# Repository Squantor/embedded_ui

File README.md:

# General purpose embedded user interface
This repository contains the files for a general purpose embedded system user interface.
## Structure
* [Electronics](https://github.com/Squantor/embedded_ui/blob/master/electronics/README.md) contains the UI PCB with LCD and buttons
* [Software](https://github.com/Squantor/embedded_ui/blob/master/software/README.md) contains the test and demo software for the user interface
* [Mechanical](https://github.com/Squantor/embedded_ui/blob/master/mechanical/README.md) contains drawings of UI covers
## Checking out
This project makes extensive use of submodules, use ```git clone --recurse-submodules https://github.com/Squantor/$(PROJECT).git``` to clone the repository and its submodules in one go.

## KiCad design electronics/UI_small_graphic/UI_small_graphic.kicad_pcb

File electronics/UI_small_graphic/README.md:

# Small graphical user interface
This PCB is a small graphical user interface with a few buttons.
# HSI (Hardware Software Interface)
This applies to a project that has a embedded software component. Describe what each pin/bus does, what it is connected to, what its function is and some "safe" behaviour when starting up.
## TODO's
Still some things need to be done:
* Produce at [Aisler](https://aisler.net/)
* Assemble
* Test & characterise
* update Readme.md with pictures and BOM
## BOM
* The standard aliexpress OLED displays with 128x64 or 128x32 resolution.
* I2C port expander (PCF device)
## Pictures
TODO

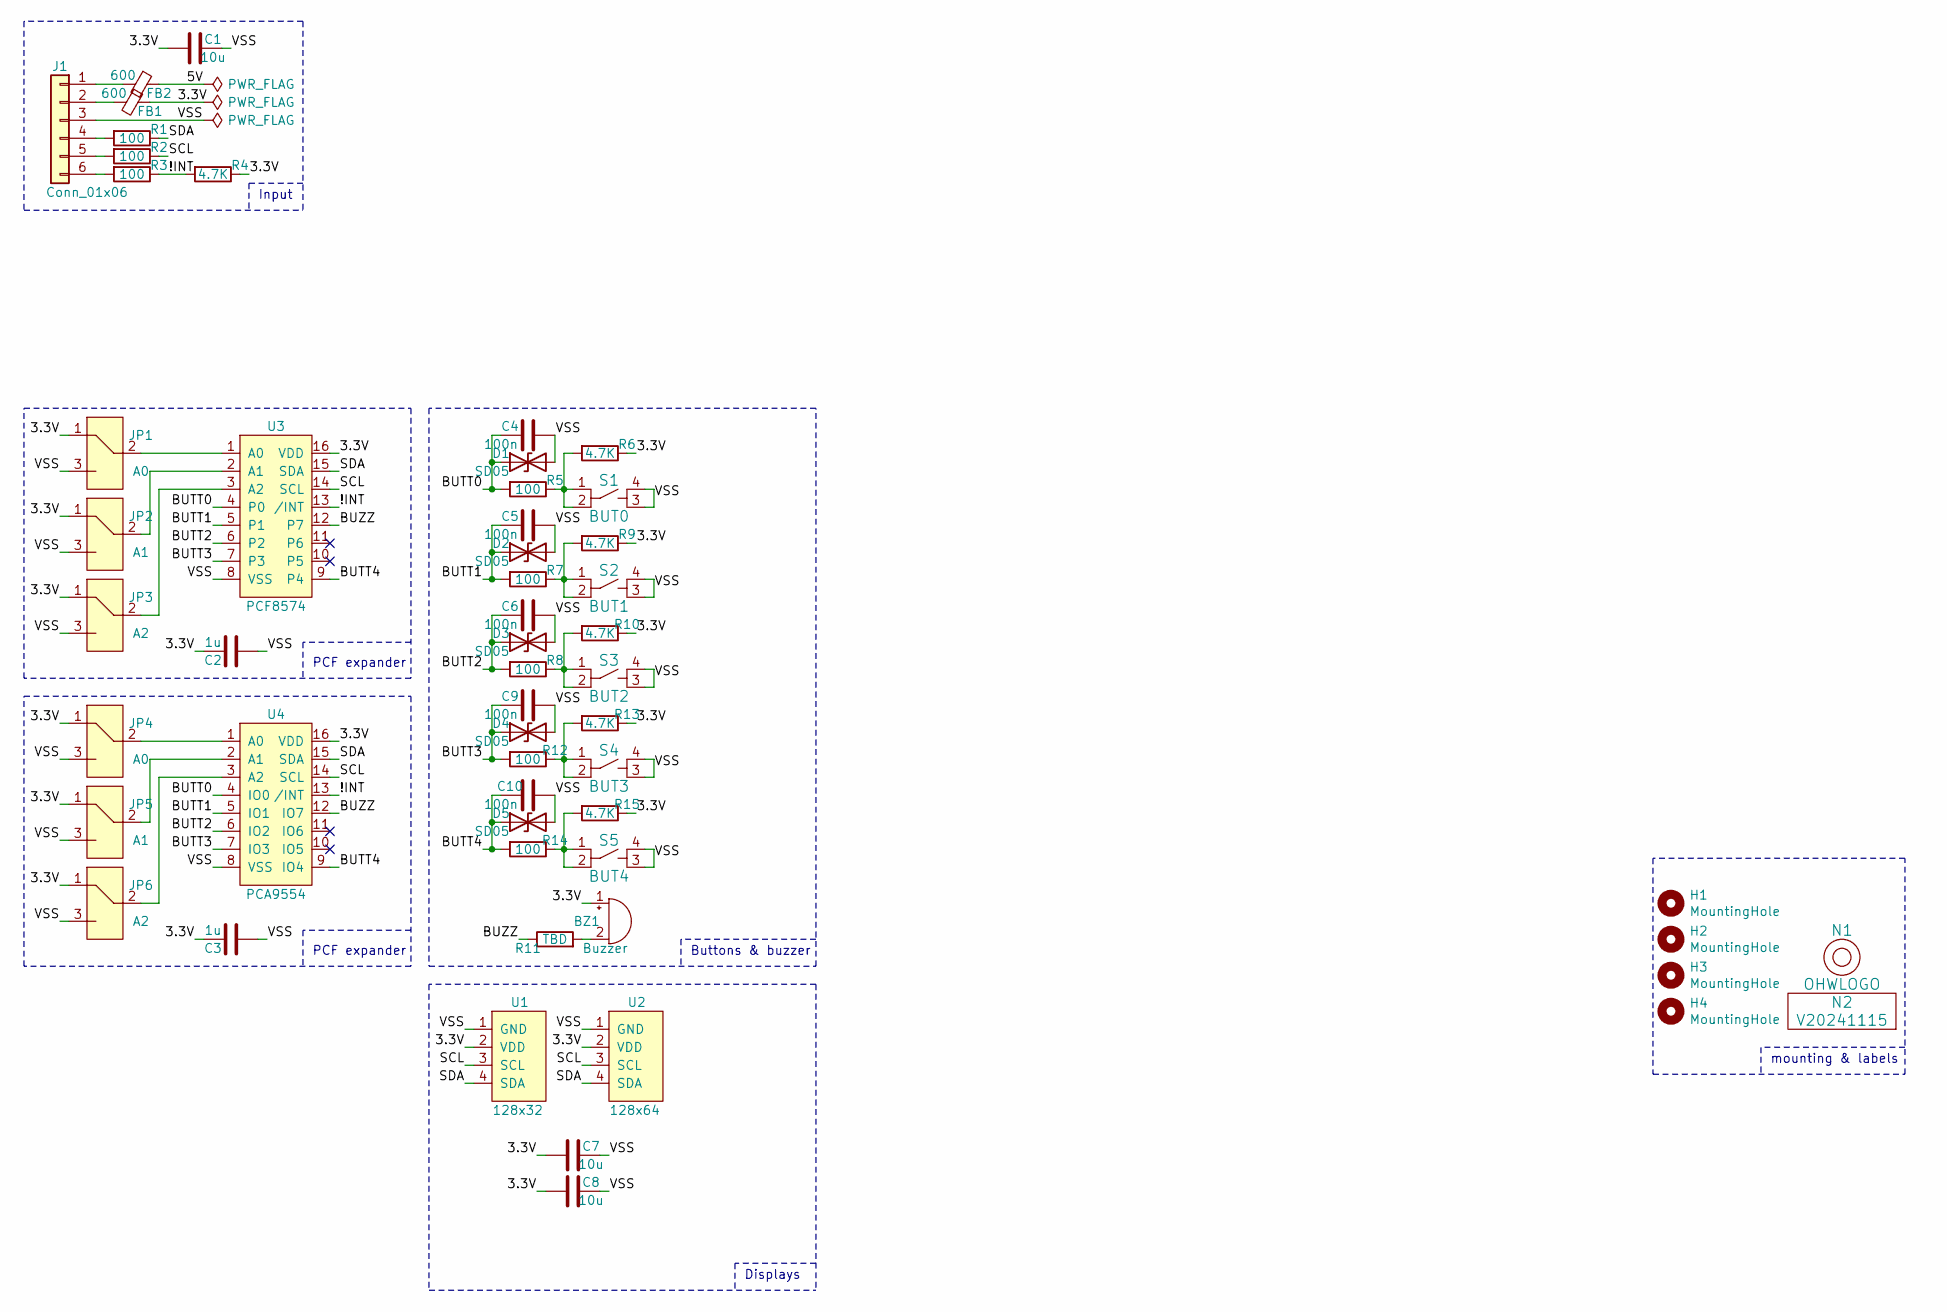
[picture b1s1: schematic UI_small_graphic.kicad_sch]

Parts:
BZ1: Buzzer; Buzzer_12x9.5RM7.6
C1, C7, C8: 10u; C_0603
C2, C3: 1u; C_0603
C4, C5, C6, C9, C10: 100n; C_0603
D1, D2, D3, D4, D5: SD05; SOD_323_onsemi
FB1, FB2: 600; L_0603
H1, H2, H3, H4: MountingHole; MountingHole_3.2mm_M3_Pad_Via
J1: Conn_01x06; JST_PH_S6B-PH-K_1x06_P2.00mm_Horizontal
JP1, JP4: A0; solder_jumper_0603_3way_12conn
JP2, JP5: A1; solder_jumper_0603_3way_12conn
JP3, JP6: A2; solder_jumper_0603_3way_12conn
N1: OHWLOGO; OSHW-Symbol_6.7x6mm_SilkScreen
N2: V20241115; Label_Generic
R1, R2, R3, R5, R7, R8, R12, R14: 100; R_0603_hand
R4, R6, R9, R10, R13, R15: 4.7K; R_0603_hand
R11: TBD; R_0603_hand
S1: BUT0; Omron_B3F-1052
S2: BUT1; Omron_B3F-1052
S3: BUT2; Omron_B3F-1052
S4: BUT3; Omron_B3F-1052
S5: BUT4; Omron_B3F-1052
U1: 128x32; OLED_128x32
U2: 128x64; OLED_132in_128x96
U3: PCF8574; SOT162-1-NXP
U4: PCA9554; SOT403-1-NXP

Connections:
/3.3V: BZ1.1 (-), C1.2, C2.1, C3.1, C7.2, C8.2, FB1.1, JP1.1, JP2.1, JP3.1, JP4.1, JP5.1, JP6.1, R4.1, R6.1, R9.1, R10.1, R13.1, R15.1, U1.2 (VDD), U2.2 (VDD), U3.16 (VDD), U4.16 (VDD)
/5V: FB2.1
/!INT: R3.1, R4.2, U3.13 (/INT), U4.13 (/INT)
/BUTT0: C4.1, D1.1 (A1), R5.2, U3.4 (P0), U4.4 (IO0)
/BUTT1: C5.1, D2.1 (A1), R7.2, U3.5 (P1), U4.5 (IO1)
/BUTT2: C6.1, D3.1 (A1), R8.2, U3.6 (P2), U4.6 (IO2)
/BUTT3: C9.1, D4.1 (A1), R12.2, U3.7 (P3), U4.7 (IO3)
/BUTT4: C10.1, D5.1 (A1), R14.2, U3.9 (P4), U4.9 (IO4)
/BUZZ: R11.1, U3.12 (P7), U4.12 (IO7)
/SCL: R2.1, U1.3 (SCL), U2.3 (SCL), U3.14 (SCL), U4.14 (SCL)
/SDA: R1.1, U1.4 (SDA), U2.4 (SDA), U3.15 (SDA), U4.15 (SDA)
/VSS: C1.1, C2.2, C3.2, C4.2, C5.2, C6.2, C7.1, C8.1, C9.2, C10.2, D1.2 (A2), D2.2 (A2), D3.2 (A2), D4.2 (A2), D5.2 (A2), J1.3, JP1.3, JP2.3, JP3.3, JP4.3, JP5.3, JP6.3, S1.3, S1.4, S2.3, S2.4, S3.3, S3.4, S4.3, S4.4, S5.3, S5.4, U1.1 (GND), U2.1 (GND), U3.8 (VSS), U4.8 (VSS)
unnamed: BZ1.2 (+), R11.2
unnamed: FB1.2, J1.2
unnamed: FB2.2, J1.1
unnamed: J1.4, R1.2
unnamed: J1.5, R2.2
unnamed: J1.6, R3.2
unnamed: JP1.2, U3.1 (A0)
unnamed: JP2.2, U3.2 (A1)
unnamed: JP3.2, U3.3 (A2)
unnamed: JP4.2, U4.1 (A0)
unnamed: JP5.2, U4.2 (A1)
unnamed: JP6.2, U4.3 (A2)
unnamed: R5.1, R6.2, S1.1, S1.2
unnamed: R7.1, R9.2, S2.1, S2.2
unnamed: R8.1, R10.2, S3.1, S3.2
unnamed: R12.1, R13.2, S4.1, S4.2
unnamed: R14.1, R15.2, S5.1, S5.2

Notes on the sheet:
Input
mounting & labels
PCF expander
Buttons & buzzer
Displays

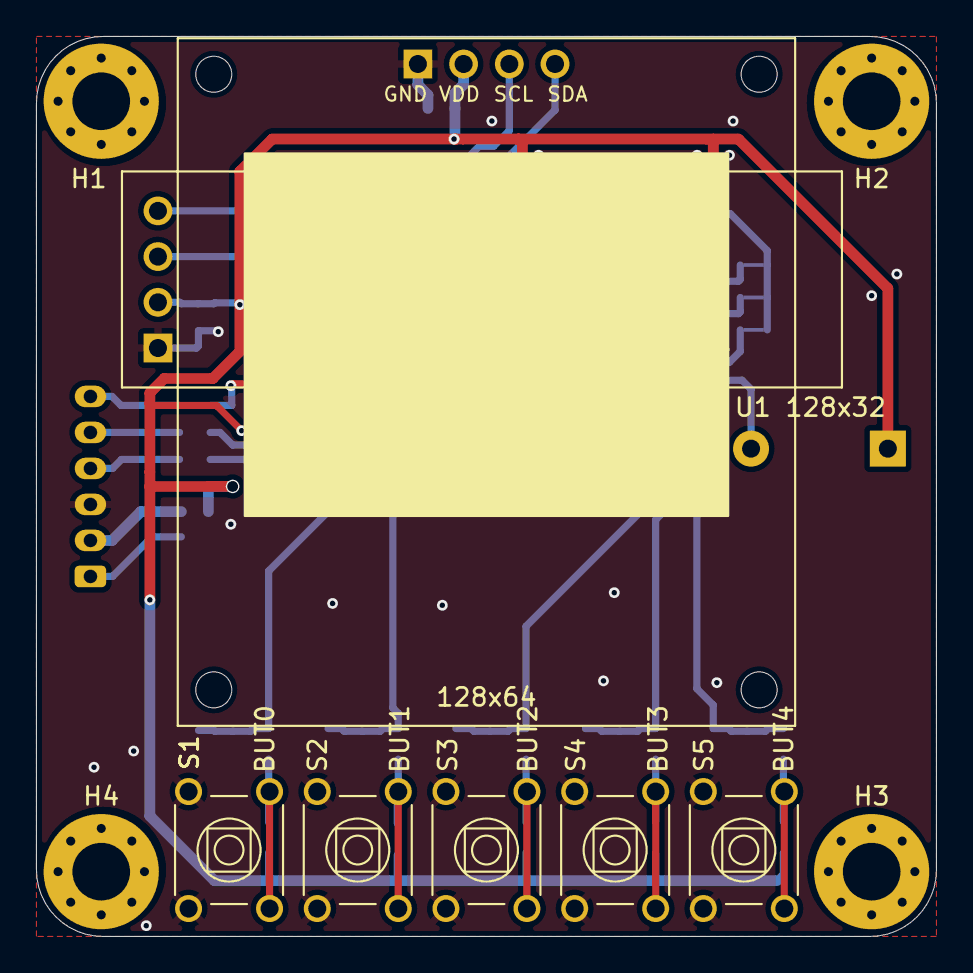
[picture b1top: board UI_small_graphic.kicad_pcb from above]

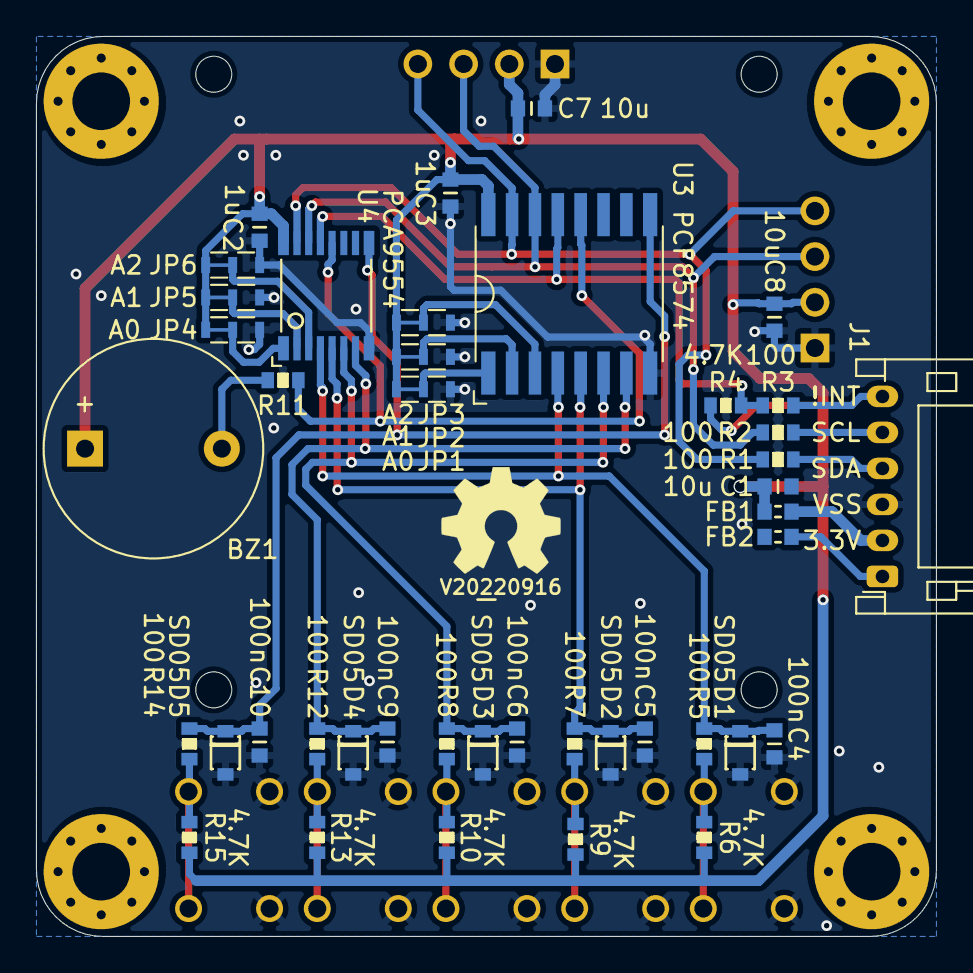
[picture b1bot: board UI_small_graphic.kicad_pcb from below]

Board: 2 copper layers, 50.0 x 50.0 mm, 55 parts (44 on the bottom side), 28 nets.

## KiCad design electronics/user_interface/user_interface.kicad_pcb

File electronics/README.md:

# Embedded User Interface hardware
Electronics for a embedded user interface.
* [user interface](user_interface/README.md) is a simple user interface for various projects.

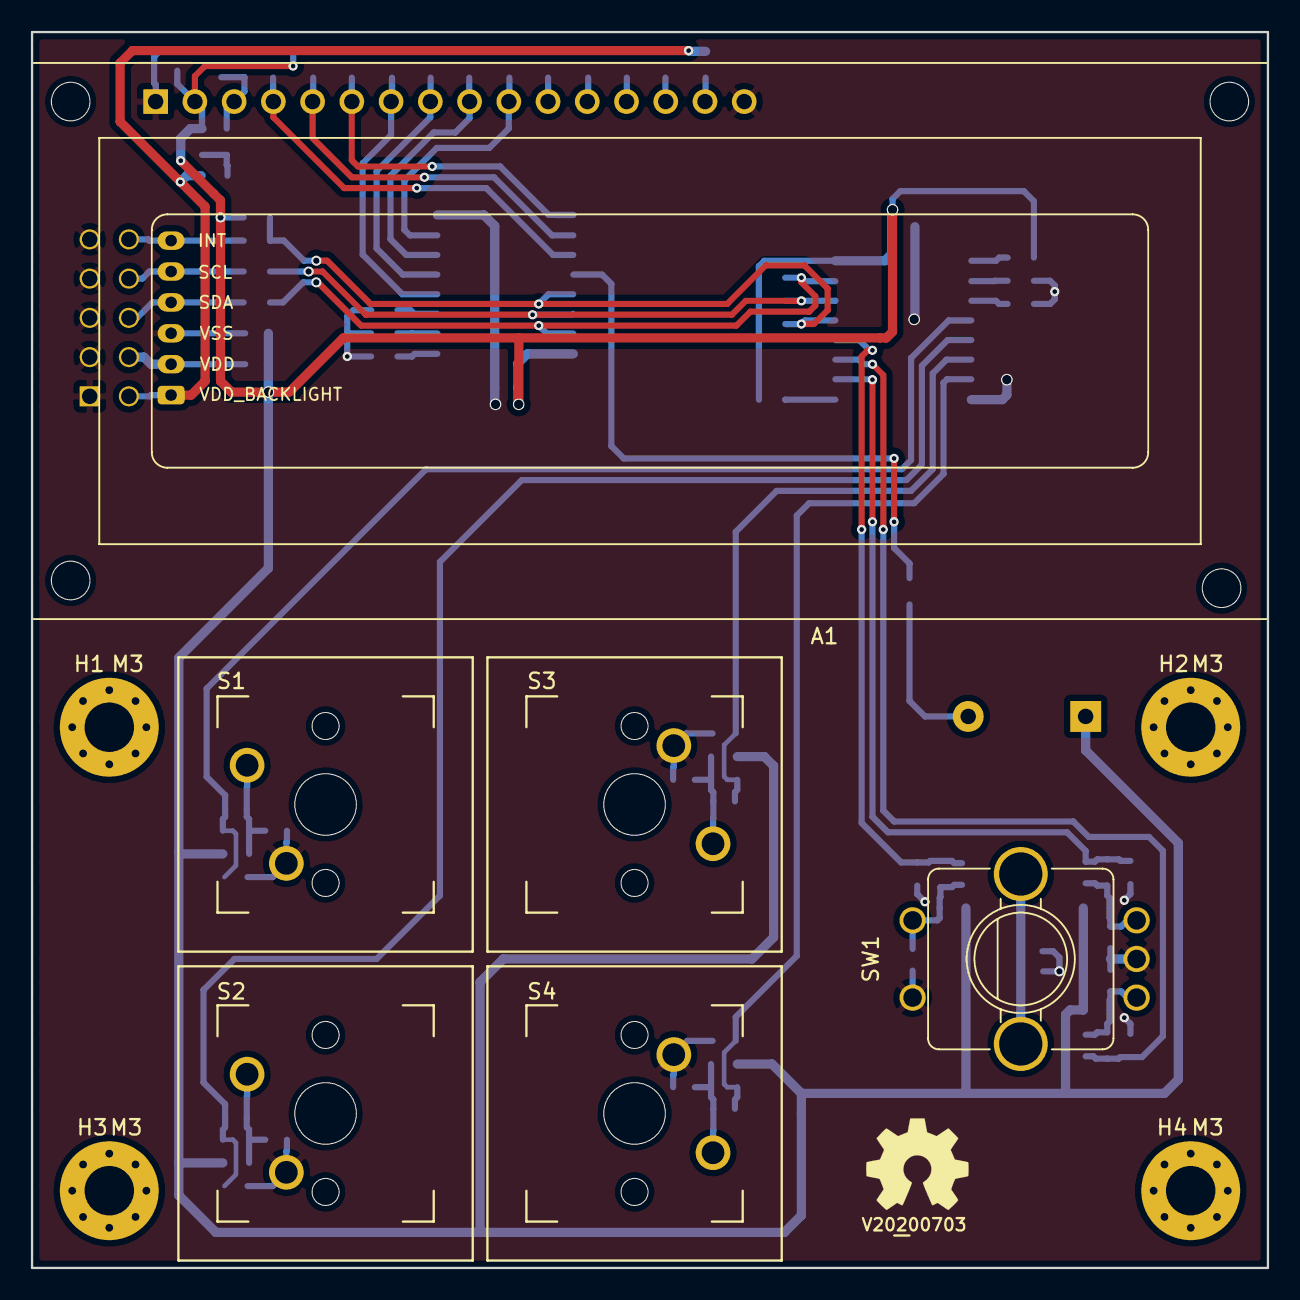
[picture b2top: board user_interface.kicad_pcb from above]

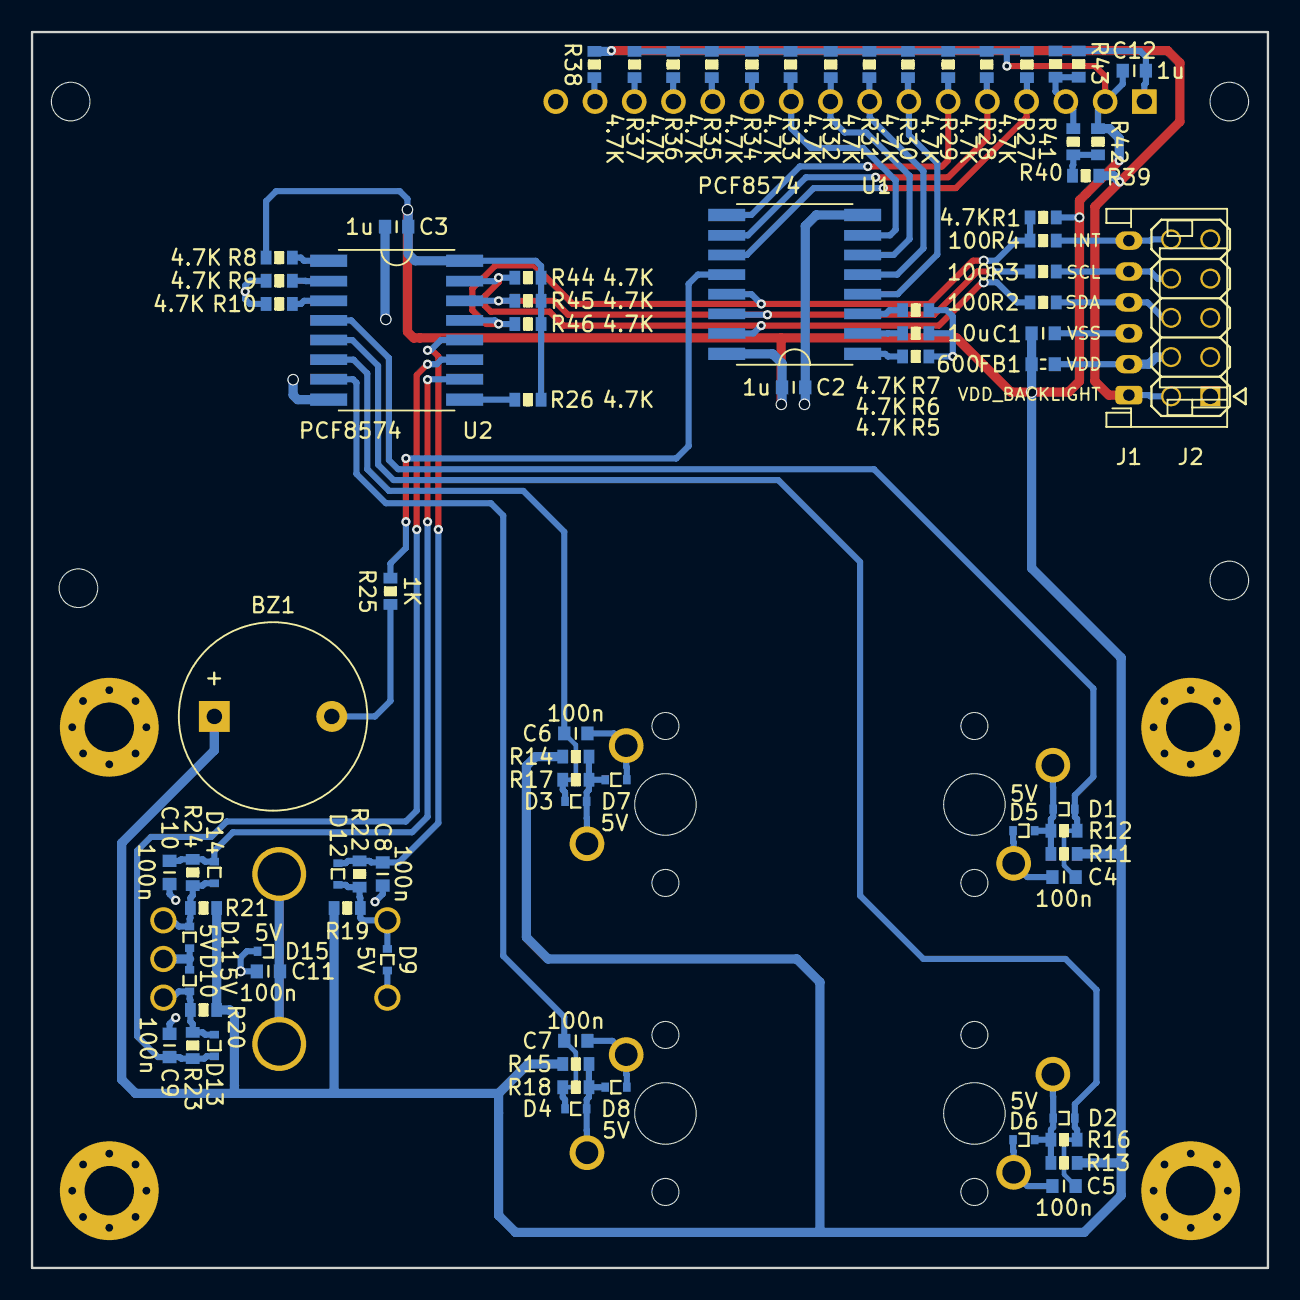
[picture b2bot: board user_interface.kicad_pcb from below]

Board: 2 copper layers, 80.0 x 80.0 mm, 91 parts (79 on the bottom side), 48 nets.

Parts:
A1: LCM1602; LCM1602K
BZ1: Buzzer; Buzzer_12x9.5RM7.6
C1: 10u; C_0603
C2, C3, C12: 1u; C_0603
C4, C5, C6, C7, C8, C9, C10, C11: 100n; C_0603
D1, D2, D3, D4, D12, D13, D14: RB521S-30; SOD-523
D5, D6, D7, D8, D9, D10, D11, D15: 5V; SOD-523
FB1: 600; L_0603
H1, H2, H3, H4: M3; MountingHole_3.2mm_M3_Pad_Via
J1: Conn_01x06; JST_PH_S6B-PH-K_1x06_P2.00mm_Horizontal
J2: Conn_02x05_Odd_Even; Header-0254-2X05-H010
N1: OHWLOGO; OSHW-Symbol_6.7x6mm_SilkScreen
N2: V20200703; Label_Generic
R1, R5, R6, R7, R8, R9, R10, R26, R27, R28, R29, R30, R31, R32, R33, R34, R35, R36, R37, R44, R45, R46: 4.7K; R_0603_hand
R2, R3, R4: 100; R_0603_hand
R11, R12, R13, R14, R15, R16, R17, R18, R19, R20, R21, R22, R23, R24, R38, R40, R41: TBD; R_0603_hand
R25: 1K; R_0603_hand
R39, R42: 0; R_0603_hand
R43: NTC?; R_0603_hand
S1, S2, S3, S4: Cherry Blue; MXOnly-1U-NoLED
SW1: ALPS_EC11E18244A5; ALPS_EC11E_style5
U1, U2: PCF8574; SOT162-1-NXP

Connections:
/!INT: R1.1, R4.1, R46.1, U1.13, U2.13
/!INT_RAW: J1.6, J2.10, R4.2
/Button_00: C4.1, D1.1, R12.1, U2.4
/Button_01: C5.1, D2.1, R16.1, U2.5
/Button_02: C6.1, D3.1, R17.1, U2.6
/Button_03: C7.1, D4.1, R18.1, U2.7
/Buzzer: R25.2, U1.12
/DB0: A1.7, R30.1, U1.4
/DB1: A1.8, R31.1, U1.5
/DB2: A1.9, R32.1, U1.6
/DB3: A1.10, R33.1, U1.7
/DB4: A1.11, R34.1
/DB5: A1.12, R35.1
/DB6: A1.13, R36.1
/DB7: A1.14, R37.1
/E: A1.6, R29.1, U1.9
/RS: A1.4, R27.1, U1.11
/RW: A1.5, R28.1, U1.10
/Rotary_A: D10.1, D13.2, R20.1, R23.2, SW1.A
/Rotary_A_filtered: C9.1, D13.1, R23.1, U2.11
/Rotary_B: D11.1, D14.2, R21.1, R24.2, SW1.B
/Rotary_B_filtered: C10.1, D14.1, R24.1, U2.10
/Rotary_push: D9.1, D12.2, R19.1, R22.2, SW1.E
/Rotary_push_filtered: C8.1, D12.1, R22.1, U2.12
/Rotary_shield: C11.2, D15.1, SW1.S
/SCL: R3.1, R45.1, U1.14, U2.14
/SCL_RAW: J1.5, J2.8, R3.2
/SDA: R2.1, R44.1, U1.15, U2.15
/SDA_RAW: J1.4, J2.6, R2.2
/VDD: A1.2, BZ1.1, C1.1, C2.1, C3.1, C12.1, FB1.1, R1.2, R8.2, R11.2, R13.2, R14.2, R15.2, R19.2, R20.2, R21.2, R26.1, R27.2, R28.2, R29.2, R30.2, R31.2, R32.2, R33.2, R34.2, R35.2, R36.2, R37.2, R42.1, R44.2, R45.2, R46.2, U1.16, U2.16
/VDD_BACKLIGHT: J1.1, J2.2, R38.2, R39.1
/VDD_RAW: FB1.2, J1.2, J2.4
/VO: A1.3, R40.2, R41.1, R43.1
/VSS: A1.1, A1.16, C1.2, C2.2, C3.2, C4.2, C5.2, C6.2, C7.2, C8.2, C9.2, C10.2, C11.1, C12.2, D5.2, D6.2, D7.2, D8.2, D9.2, D10.2, D11.2, D15.2, J1.3, J2.1, J2.3, J2.5, J2.7, J2.9, R5.2, R6.2, R7.2, R9.2, R10.2, R41.2, R43.2, S1.1, S2.1, S3.1, S4.1, SW1.C, SW1.D, U1.8, U2.8
unnamed: A1.15, R38.1
unnamed: BZ1.2, R25.1
unnamed: D1.2, D5.1, R11.1, R12.2, S1.2
unnamed: D2.2, D6.1, R13.1, R16.2, S2.2
unnamed: D3.2, D7.1, R14.1, R17.2, S3.2
unnamed: D4.2, D8.1, R15.1, R18.2, S4.2
unnamed: R5.1, U1.1
unnamed: R6.1, U1.2
unnamed: R7.1, U1.3
unnamed: R8.1, U2.1
unnamed: R9.1, U2.2
unnamed: R10.1, U2.3
unnamed: R26.2, U2.9
unnamed: R39.2, R40.1, R42.2

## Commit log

2020-06-19 added initial project landing
2020-06-19 initial loadout of documentation
2020-06-19 renamed file
2020-06-19 added software submodules
2020-06-19 added gitignore
2020-06-19 initial loading of template
2020-06-19 added component libraries
2020-06-19 added user interface hardware (from the soldering station
2020-07-03 updated versionnumber
2020-07-03 changed default font size for silk layer
2020-07-03 WIP adding labels to connectors
2020-07-03 WIP labels now on top layer too, placement completed, time to route
2020-07-03 routing done
2020-07-03 minor silk placement
2021-11-12 removing old submodule URLS
2021-11-12 added new submodules
2021-11-12 updated libraries
2022-01-28 updated submodules for new board
2022-02-01 started with small userinterface
2022-02-01 renamed first user interface
2022-02-01 updated description of the big user interface
2022-02-01 started with PCB dimensions and input connector
2022-02-02 added displays to board
2022-02-07 added PCA I/O expander
2022-02-07 updated footprints
2022-02-07 added I2C port expanders to PCB
2022-02-07 routing
2022-02-07 further routing
2022-02-10 added buzzer
2022-02-10 numbering
2022-02-11 routing completed
2022-02-11 routing completed, added decoupling caps for displays, started with silk placement
2022-02-13 added new versionnumber, updated silk placement top, WIP bottom
2022-02-13 bottom silk placed
2022-02-17 small changes preparing for production
2022-03-08 updated schematic
2022-03-08 updated PCB library
2022-03-10 generated plots
2022-03-10 updated plot settings
2022-03-21 added template parametric box
2022-03-21 added freecad stuff to ignores
2022-03-21 connector hole better position
2022-04-05 small UI modification?
2022-04-05 fixed UI dimensions
2022-04-05 updated PCB library
2022-04-22 fixing build errors
2022-04-22 updated to new build system
2022-04-22 further updates to build system, damn it was old
2022-04-22 updated vscode settings
2022-04-22 added embedded ui mini test program
2022-04-22 updated git ignore with new buildsystem ignores
2022-04-24 updated libmcull
2022-04-25 fixed build errors
2022-04-25 removed old gdb scripts
2022-04-25 debugging now works, more or less
2022-04-25 got USART output working correctly, ported over SSD1306 demo
2022-04-29 added USUART divider magic number
2022-04-29 switching over to event based handling
2022-04-29 transformed application into a class
2022-04-29 added empty button handler method, but first need to update libmcull
2022-04-30 updated libmcull to have the pin interrupts for LPC8XX
2022-05-06 WIP button handling
2022-05-08 I2C readout
2022-06-03 conversion to kicad 6
2022-06-03 button handling stuff
2022-06-03 updated versionnumber, fixed DRC errors
2022-06-03 fixed via
2022-06-03 fixed 3d models
2022-06-03 pcb component updates
2022-06-04 updated SSD1306 libraries
2022-06-04 switched to framebuffered SSD1306 driver
2022-06-04 updated to newer SSD1306 API
2022-06-04 added segger debugging target
2022-06-04 fixed redundant setting
2022-06-05 changed to different style of launch target in cortex-debug
2022-06-05 added breakpoint at main
2022-06-10 Work in progress on Menu
2022-06-10 WIP menu rendering
2022-06-10 made a selectable option
2022-07-24 updated library
2022-07-24 fixed footprint library
2022-07-29 updated demo
2022-07-29 switched buttons
2022-07-29 added 2 buttons extra, we have space for them
2022-07-29 added new displays and addional buttons
2022-08-28 placed ESD parts, silk placed
2024-11-15 updated to new kicad version, updated mechanical dimensions to newer nuclone hole pattern
